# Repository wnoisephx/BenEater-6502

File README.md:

A KiCad PCB layout for Ben Eater's 6502 computer with some minor updates and an expanded I/O

The board is layed out in such a way as to allow you to follow along with the Ben's build videos

https://eater.net/

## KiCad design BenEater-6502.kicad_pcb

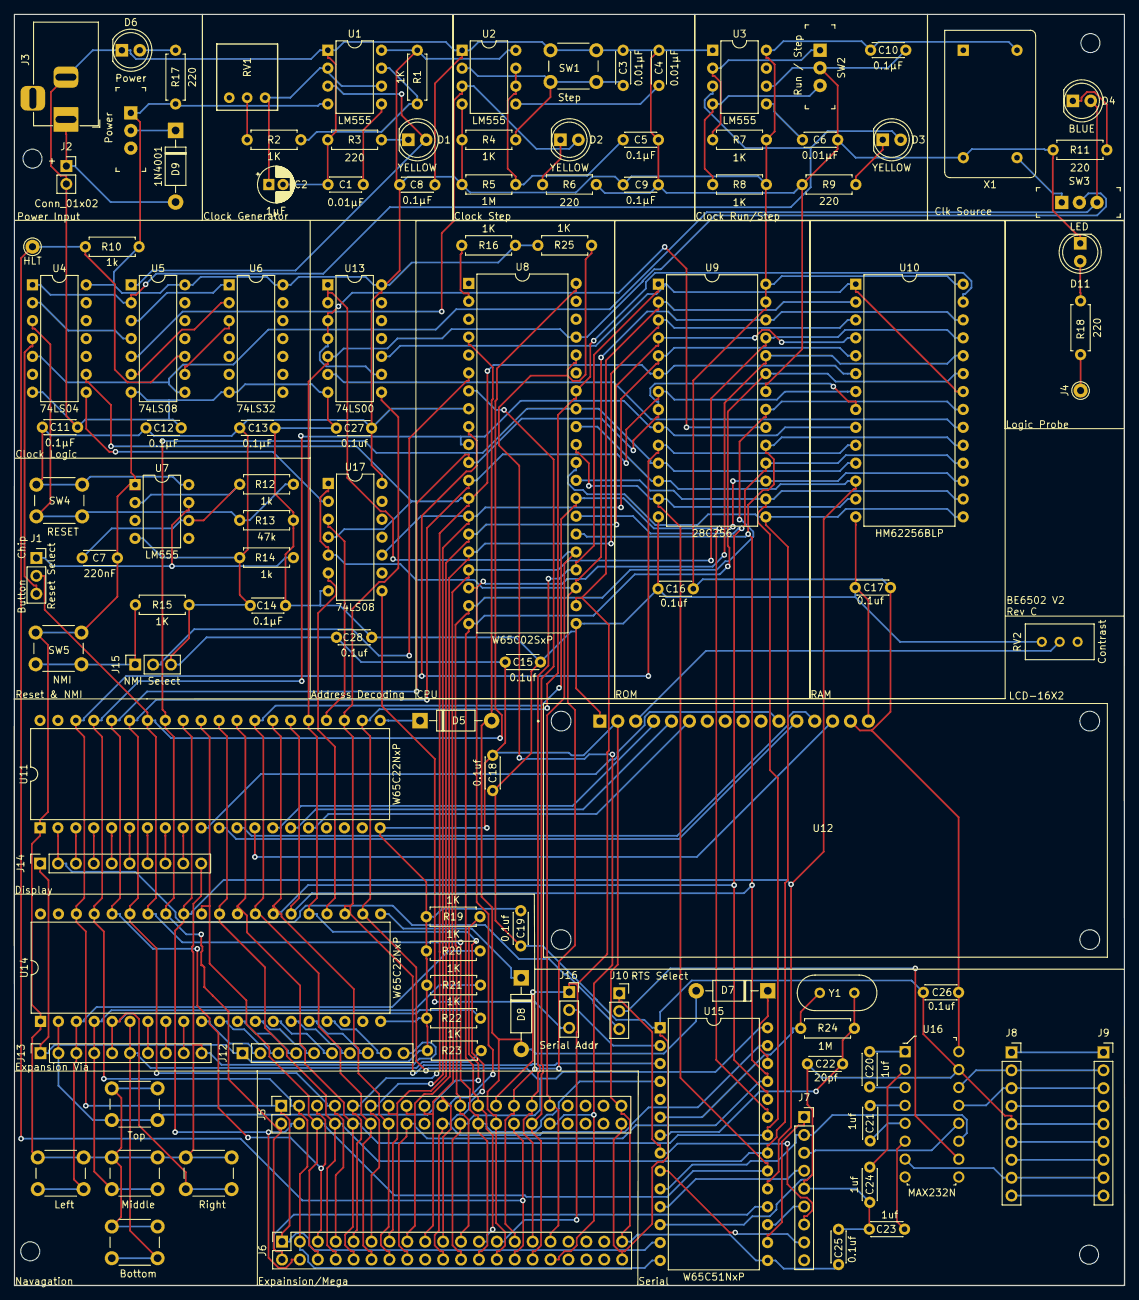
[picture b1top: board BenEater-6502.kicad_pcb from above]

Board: 2 copper layers, 157.5 x 180.3 mm, 115 parts (0 on the bottom side), 135 nets.

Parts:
Bottom1: Bottom; SW_PUSH_6mm_H5mm
BottomLeft: MountingHole_2.7mm
BottomRight: MountingHole_2.7mm
C1, C3, C4, C6: 0.01µF; C_Disc_D4.3mm_W1.9mm_P5.00mm
C2: 1µF; CP_Radial_D5.0mm_P2.00mm
C5, C8, C9, C10, C11, C12, C13, C14: 0.1µF; C_Disc_D4.3mm_W1.9mm_P5.00mm
C7: 220nF; C_Disc_D4.3mm_W1.9mm_P5.00mm
C15, C16, C17, C18, C19, C25, C26, C27, C28: 0.1uf; C_Disc_D4.3mm_W1.9mm_P5.00mm
C20, C21, C23, C24: 1uf; C_Disc_D4.3mm_W1.9mm_P5.00mm
C22: 20pf; C_Disc_D4.3mm_W1.9mm_P5.00mm
D1, D2, D3: YELLOW; LED_D5.0mm
D4: BLUE; LED_D5.0mm
D5, D7, D8: SB140; D_DO-41_SOD81_P10.16mm_Horizontal
D6: Power; LED_D5.0mm
D9: 1N4001; D_DO-41_SOD81_P10.16mm_Horizontal
D11: LED; LED_D5.0mm
J1: Conn_01x03_Pin; PinSocket_1x03_P2.54mm_Vertical
J2: Conn_01x02; PinSocket_1x02_P2.54mm_Vertical
J3: Barrel Jack; BarrelJack_Horizontal
J4: Logic Probe; Pin_D1.0mm_L10.0mm
J5, J6: Conn_02x20_Counter_Clockwise; PinSocket_2x20_P2.54mm_Vertical
J7, J8, J9: Conn_01x09; PinSocket_1x09_P2.54mm_Vertical
J10: RTS Select; PinSocket_1x03_P2.54mm_Vertical
J11: HLT; Pin_D1.0mm_L10.0mm
J12, J13, J14: Conn_01x10; PinSocket_1x10_P2.54mm_Vertical
J15: NMI Select; PinSocket_1x03_P2.54mm_Vertical
J16: Serial Addr; PinSocket_1x03_P2.54mm_Vertical
Left1: Left; SW_PUSH_6mm_H5mm
Middle1: Middle; SW_PUSH_6mm_H5mm
R1, R2, R4, R7, R8, R15, R16, R19, R20, R21, R22, R23, R25: 1K; R_Axial_DIN0207_L6.3mm_D2.5mm_P7.62mm_Horizontal
R3, R6, R9, R11, R17, R18: 220; R_Axial_DIN0207_L6.3mm_D2.5mm_P7.62mm_Horizontal
R5, R24: 1M; R_Axial_DIN0207_L6.3mm_D2.5mm_P7.62mm_Horizontal
R10, R12, R14: 1k; R_Axial_DIN0207_L6.3mm_D2.5mm_P7.62mm_Horizontal
R13: 47k; R_Axial_DIN0207_L6.3mm_D2.5mm_P7.62mm_Horizontal
RV1: 1M; Potentiometer-5.5mm
RV2: Contrast; Potentiometer_Bourns_3386C_Horizontal
Right1: Right; SW_PUSH_6mm_H5mm
SW1: Step; SW_PUSH_6mm_H5mm
SW2: Run / Step; Switch_Slide_11.6x4mm_EG1218
SW3: Clk Source; Switch_Slide_11.6x4mm_EG1218
SW4: RESET; SW_PUSH_6mm_H5mm
SW5: NMI; SW_PUSH_6mm_H5mm
SW6: Power; Switch_Slide_11.6x4mm_EG1218
Top1: Top; SW_PUSH_6mm_H5mm
TopLeft: MountingHole_2.7mm
TopRight: MountingHole_2.7mm
U1, U2, U3, U7: LM555; DIP-8_W7.62mm
U4: 74LS04; DIP-14_W7.62mm
U5, U17: 74LS08; DIP-14_W7.62mm
U6: 74LS32; DIP-14_W7.62mm
U8: W65C02SxP; DIP-40_W15.24mm
U9: 28C256; DIP-28_W15.24mm
U10: HM62256BLP; DIP-28_W15.24mm
U11, U14: W65C22NxP; DIP-40_W15.24mm
U12: LCD-16X2; MODULE_LCD-16X2
U13: 74LS00; DIP-14_W7.62mm
U15: W65C51NxP; DIP-28_W15.24mm
U16: MAX232N; DIP-16_W7.62mm
X1: ACO-xxxMHz; Oscillator_DIP-14
Y1: Crystal; Crystal_HC18-U_Vertical

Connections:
+5V: C8.1, C9.1, C10.1, C11.1, C12.1, C13.1, C14.1, C15.1, C16.1, C17.1, C18.1, C19.1, C25.1, C26.1, C27.1, C28.1, J5.39, J6.39, J12.1, J13.1, J14.1, J15.3, R1.1, R4.1, R5.1, R7.1, R8.1, R10.1, R14.1, R15.2, R16.1, R17.1, R19.2, R20.2, R21.2, R22.2, R23.2, R25.1, SW4.1, SW6.1 (A), U1.4 (R), U1.8 (VCC), U2.4 (R), U2.8 (VCC), U3.8 (VCC), U4.14 (VCC), U5.14 (VCC), U6.14 (VCC), U7.4 (R), U7.8 (VCC), U8.8 (VDD), U9.27 (~WE), U9.28 (VCC), U10.28 (VCC), U11.20 (VCC), U12.2 (VDD), U12.15 (A), U13.14 (VCC), U14.20 (VCC), U15.15 (VCC), U16.16 (VCC), U17.14 (VCC), X1.14 (Vcc)
/A0: J5.1, J6.1, U8.9 (A0), U9.10 (A0), U10.10 (A0), U11.38 (RS0), U14.38 (RS0), U15.13 (RS0)
/A1: J5.3, J6.3, U8.10 (A1), U9.9 (A1), U10.9 (A1), U11.37 (RS1), U14.37 (RS1), U15.14 (RS1)
/A2: J5.5, J6.5, U8.11 (A2), U9.8 (A2), U10.8 (A2), U11.36 (RS2), U14.36 (RS2)
/A3: J5.7, J6.7, U8.12 (A3), U9.7 (A3), U10.7 (A3), U11.35 (RS3), U14.35 (RS3)
/A4: J5.9, J6.9, U4.9, U8.13 (A4), U9.6 (A4), U10.6 (A4), U17.4
/A5: J5.11, J6.11, U8.14 (A5), U9.5 (A5), U10.5 (A5), U17.10
/A6: J5.13, J6.13, U8.15 (A6), U9.4 (A6), U10.4 (A6)
/A7: J5.15, J6.15, U8.16 (A7), U9.3 (A7), U10.3 (A7)
/A8: J5.17, J6.17, U8.17 (A8), U9.25 (A8), U10.25 (A8)
/A9: J5.19, J6.19, U8.18 (A9), U9.24 (A9), U10.24 (A9)
/A10: J5.21, J6.21, U8.19 (A10), U9.21 (A10), U10.21 (A10)
/A11: J5.23, J6.23, U8.20 (A11), U9.23 (A11), U10.23 (A11)
/A12: J5.25, J6.25, J16.1, U8.22 (A12), U9.2 (A12), U10.2 (A12)
/A13: J5.27, J6.27, U8.23 (A13), U9.26 (A13), U10.26 (A13), U17.1, U17.5
/A14: J5.29, J6.29, U8.24 (A14), U9.1 (A14), U10.1 (A14), U10.22 (~OE), U13.10
/A15: J5.31, J6.31, U8.25 (A15), U13.1, U13.2
/BE: J5.32, J6.32, R25.2, U8.36 (BE)
/CLK: J5.20, J6.20, SW3.2 (B), U8.37 (ϕ0), U11.25 (ϕ2), U13.5, U14.25 (ϕ2), U15.27 (ϕ2)
/CS1Serial: J16.2, U15.2 (CS1)
/CS1Via1: U11.24 (CS1), U17.3
/CS1Via2: U14.24 (CS1), U17.6
/CS2: U11.23 (~CS2), U13.8, U14.23 (~CS2), U15.3 (~CS2)
/D0: J5.2, J6.2, U8.33 (D0), U9.11 (D0), U10.11 (Q0), U11.33 (D0), U14.33 (D0), U15.18 (D0)
/D1: J5.4, J6.4, U8.32 (D1), U9.12 (D1), U10.12 (Q1), U11.32 (D1), U14.32 (D1), U15.19 (D1)
/D2: J5.6, J6.6, U8.31 (D2), U9.13 (D2), U10.13 (Q2), U11.31 (D2), U14.31 (D2), U15.20 (D2)
/D3: J5.8, J6.8, U8.30 (D3), U9.15 (D3), U10.15 (Q3), U11.30 (D3), U14.30 (D3), U15.21 (D3)
/D4: J5.10, J6.10, U8.29 (D4), U9.16 (D4), U10.16 (Q4), U11.29 (D4), U14.29 (D4), U15.22 (D4)
/D5: J5.12, J6.12, U8.28 (D5), U9.17 (D5), U10.17 (Q5), U11.28 (D5), U14.28 (D5), U15.23 (D5)
/D6: J5.14, J6.14, U8.27 (D6), U9.18 (D6), U10.18 (Q6), U11.27 (D6), U14.27 (D6), U15.24 (D6)
/D7: J5.16, J6.16, U8.26 (D7), U9.19 (D7), U10.19 (Q7), U11.26 (D7), U14.26 (D7), U15.25 (D7)
/HLT: J5.28, J6.28, J11.1, R10.2, U5.10
/IRQ: D5.2 (A), D7.2 (A), D8.2 (A), J5.26, J6.26, U8.4 (~IRQ)
/RAMCS: U10.20 (~CS), U13.6
/ROMCS: U9.20 (~CS), U13.3, U13.4, U13.9
/RTSVia: J10.3, J14.2, U11.2 (PA0)
/Reset: J1.2, J5.24, J6.24, U8.40 (~RES), U11.34 (~RES), U14.34 (~RES), U15.4 (~RES)
/R/W: J5.22, J6.22, U8.34 (R/~W), U10.27 (~WE), U11.22 (R/~W), U14.22 (R/~W), U15.28 (R/~W)
/Sync: J5.30, J6.30, U8.7 (SYNC)
Earth: Bottom1.1, C1.2, C2.2, C3.2, C4.2, C5.2, C6.2, C7.2, C8.2, C9.2, C10.2, C11.2, C12.2, C13.2, C14.2, C15.2, C16.2, C17.2, C18.2, C19.2, C22.2, C23.2, C24.2, C25.2, C26.2, C27.2, C28.2, D6.1 (K), D11.1 (K), J2.2, J3.2, J5.40, J6.40, J7.5, J8.5, J9.5, J12.10, J13.10, J14.10, Left1.1, Middle1.1, R3.1, R6.1, R9.1, R11.2, R13.2, RV2.1, Right1.1, SW1.1, SW2.2 (B), SW5.1, Top1.1, U1.1 (GND), U2.1 (GND), U3.1 (GND), U3.6 (THR), U4.7 (GND), U5.7 (GND), U6.7 (GND), U7.1 (GND), U8.21 (VSS), U9.14 (GND), U9.22 (~OE), U10.14 (GND), U11.1 (VSS), U12.1 (VSS), U12.16 (K), U13.7 (GND), U14.1 (VSS), U15.1 (VSS), U16.15 (GND), U17.7 (GND), X1.7 (GND)
unnamed: D1.2 (A), U1.3 (Q), U5.1
unnamed: D1.1 (K), R3.2
unnamed: D2.2 (A), U2.3 (Q), U5.5
unnamed: D2.1 (K), R6.2
unnamed: D3.2 (A), U3.3 (Q), U4.1, U5.2
unnamed: D3.1 (K), R9.2
unnamed: D4.2 (A), SW3.3 (C), U4.5, U5.8
unnamed: D4.1 (K), R11.1
unnamed: D5.1 (K), U11.21 (~IRQ)
unnamed: D6.2 (A), R17.2
unnamed: D7.1 (K), U15.26 (~IRQ)
unnamed: D8.1 (K), U14.21 (~IRQ)
unnamed: D9.2 (A), J2.1, J3.1
unnamed: D9.1 (K), SW6.2 (B)
unnamed: D11.2 (A), R18.2
unnamed: J1.1, R14.2, U7.7 (DIS)
unnamed: J1.3, U4.4
unnamed: J4.1, R18.1
unnamed: J7.1, U15.16 (~DCD)
unnamed: J7.2, U15.10 (TxD), U16.11 (T1IN)
unnamed: J7.3, U15.12 (RxD), U16.12 (R1OUT)
unnamed: J7.4, U15.11 (~DTR)
unnamed: J7.6, U15.17 (~DSR)
unnamed: J7.8, U15.9 (~CTS)
unnamed: J8.1, J9.1
unnamed: J8.2, J9.2, U16.14 (T1OUT)
unnamed: J8.3, J9.3, U16.13 (R1IN)
unnamed: J8.4, J9.4
unnamed: J8.6, J9.6
unnamed: J8.7, J9.7
unnamed: J8.8, J9.8, U16.7 (T2OUT)
unnamed: J8.9, J9.9
unnamed: J7.7, J10.1, U15.8 (~RTS)
unnamed: J10.2, U16.10 (T2IN)
unnamed: J12.2, U14.10 (PB0)
unnamed: J12.3, U14.11 (PB1)
unnamed: J12.4, U14.12 (PB2)
unnamed: J12.5, U14.13 (PB3)
unnamed: J12.6, U14.14 (PB4)
unnamed: J12.7, U14.15 (PB5)
unnamed: J12.8, U14.16 (PB6)
unnamed: J12.9, U14.17 (PB7)
unnamed: J13.2, R19.1, Top1.2, U14.2 (PA0)
unnamed: J13.3, Left1.2, R20.1, U14.3 (PA1)
unnamed: J13.4, Middle1.2, R21.1, U14.4 (PA2)
unnamed: J13.5, R22.1, Right1.2, U14.5 (PA3)
unnamed: Bottom1.2, J13.6, R23.1, U14.6 (PA4)
unnamed: J13.7, U14.7 (PA5)
unnamed: J13.8, U14.8 (PA6)
unnamed: J13.9, U14.9 (PA7)
unnamed: J14.3, U11.3 (PA1)
unnamed: J14.4, U11.4 (PA2)
unnamed: J14.5, U11.5 (PA3)
unnamed: J14.6, U11.6 (PA4)
unnamed: J14.7, U11.7 (PA5)
unnamed: J14.8, U11.8 (PA6)
unnamed: J14.9, U11.9 (PA7)
unnamed: J15.1, R15.1, SW5.2
unnamed: J15.2, U8.6 (~NMI)
unnamed: J16.3, U17.8
unnamed: R2.1, RV1.2
unnamed: R12.2, R13.1, SW4.2, U4.3
unnamed: R7.2, SW2.1 (A), U3.2 (TR)
unnamed: R8.2, SW2.3 (C), U3.4 (R)
unnamed: SW3.1 (A), X1.8 (OUT)
unnamed: C1.1, U1.5 (CV)
unnamed: R1.2, R2.2, U1.7 (DIS)
unnamed: C2.1, RV1.1, U1.2 (TR), U1.6 (THR)
unnamed: C4.1, U2.5 (CV)
unnamed: C5.1, R5.2, U2.6 (THR), U2.7 (DIS)
unnamed: C3.1, R4.2, SW1.2, U2.2 (TR)
unnamed: C6.1, U3.5 (CV)
unnamed: U4.2, U5.4
unnamed: U5.3, U6.1
unnamed: U5.6, U6.2
unnamed: U5.9, U6.3
unnamed: C7.1, R12.1, U7.2 (TR), U7.6 (THR)
unnamed: R16.2, U8.2 (RDY)
unnamed: U11.10 (PB0), U12.11 (DB4)
unnamed: U11.11 (PB1), U12.12 (DB5)
unnamed: U11.12 (PB2), U12.13 (DB6)
unnamed: U11.13 (PB3), U12.14 (DB7)
unnamed: U11.14 (PB4), U12.4 (RS)
unnamed: U11.15 (PB5), U12.5 (R/W)
unnamed: U11.16 (PB6), U12.6 (E)
unnamed: RV2.2, U12.3 (VO)
unnamed: R24.2, U15.6 (XTAL1), Y1.2
unnamed: C22.1, R24.1, U15.7 (XTAL2), Y1.1
unnamed: C20.2, U16.1 (C1+)
unnamed: C20.1, U16.3 (C1-)
unnamed: C21.2, U16.4 (C2+)
unnamed: C21.1, U16.5 (C2-)
unnamed: C24.1, U16.2 (VS+)
unnamed: C23.1, U16.6 (VS-)
unnamed: U4.8, U17.2

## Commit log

2024-09-17 Initial commit rev 0.5
2024-09-19 Add TODO
2024-10-17 intermediate commit
2024-10-23 interm commit
2024-10-24 An other interm relase
2024-10-24 Getting closer
2024-11-05 Fix Oops...
2024-11-17 Closer yet
2024-11-18 Fixed the addressing Still not fixed
2024-11-19 updated plots
2024-12-23 It works
2024-12-23 file clean up
2024-12-23 more file cleanup
